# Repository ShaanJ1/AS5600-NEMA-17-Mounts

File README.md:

# AS5600 Nema 17 Mounts

Mounting hardware for attaching the AS5600 rotary encoder onto the back of the NEMA 17 stepper motor
Includes a magnet centering jig which helps you properly center the magnet onto the rear shaft to glue it in place

## Mounting Options:
### 1. Custom PCB + Spacers
Parts required:
- Diametric magnet
- Super glue (or equivalent strong adhesive)
- 4x M3 Machine Screws
- Custom AS5600 breakout board
- 4x Spacers

Installation Steps:

### 2. Custom mount for the AS5600
Parts Required:
- Diametric magnet
- Super glue (or equivalent strong adhesive)
- 3D printed sensor housing
- Regular AS5600 PCB
- 4x M2.5 screws

Installation Steps:

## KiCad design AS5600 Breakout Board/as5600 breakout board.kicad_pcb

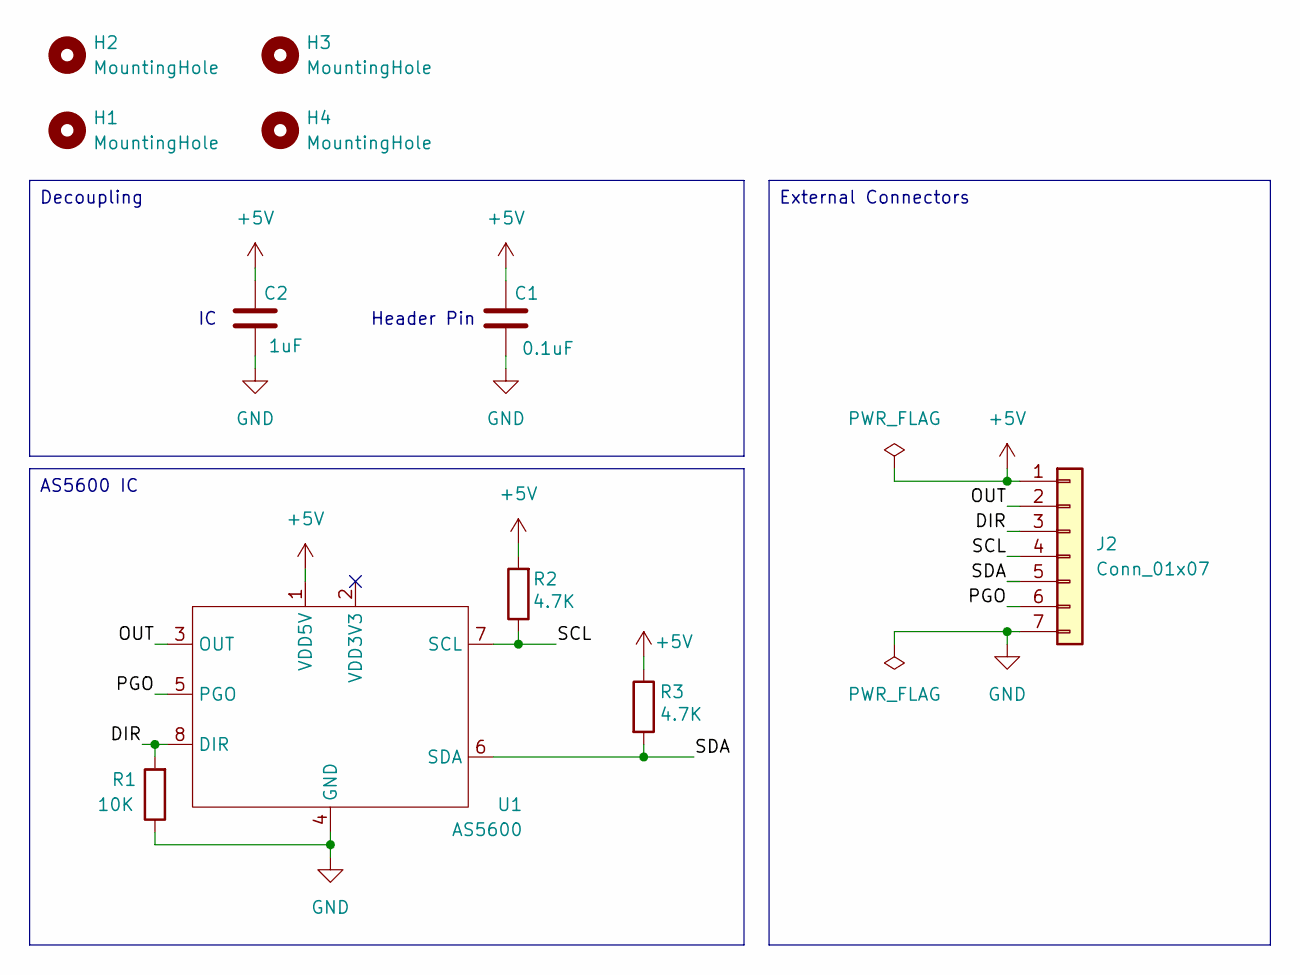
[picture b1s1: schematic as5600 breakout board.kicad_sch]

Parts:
C1: 0.1uF; C_0603_1608Metric
C2: 1uF; C_0603_1608Metric
H1, H2, H3, H4: MountingHole; MountingHole_3.2mm_M3
J2: Conn_01x07; PinHeader_1x07_P2.54mm_Horizontal
R1: 10K; R_0603_1608Metric
R2, R3: 4.7K; R_0603_1608Metric
U1: AS5600; SOIC-8_3.9x4.9mm_P1.27mm

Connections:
+5V: C1.1, C2.1, J2.1, R2.2, R3.1, U1.1 (VDD5V)
/DIR: J2.3, R1.2, U1.8 (DIR)
/OUT: J2.2, U1.3 (OUT)
/PGO: J2.6, U1.5 (PGO)
/SCL: J2.4, R2.1, U1.7 (SCL)
/SDA: J2.5, R3.2, U1.6 (SDA)
GND: C1.2, C2.2, J2.7, R1.1, U1.4 (GND)

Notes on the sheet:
Header Pin
Decoupling
External Connectors
AS5600 IC

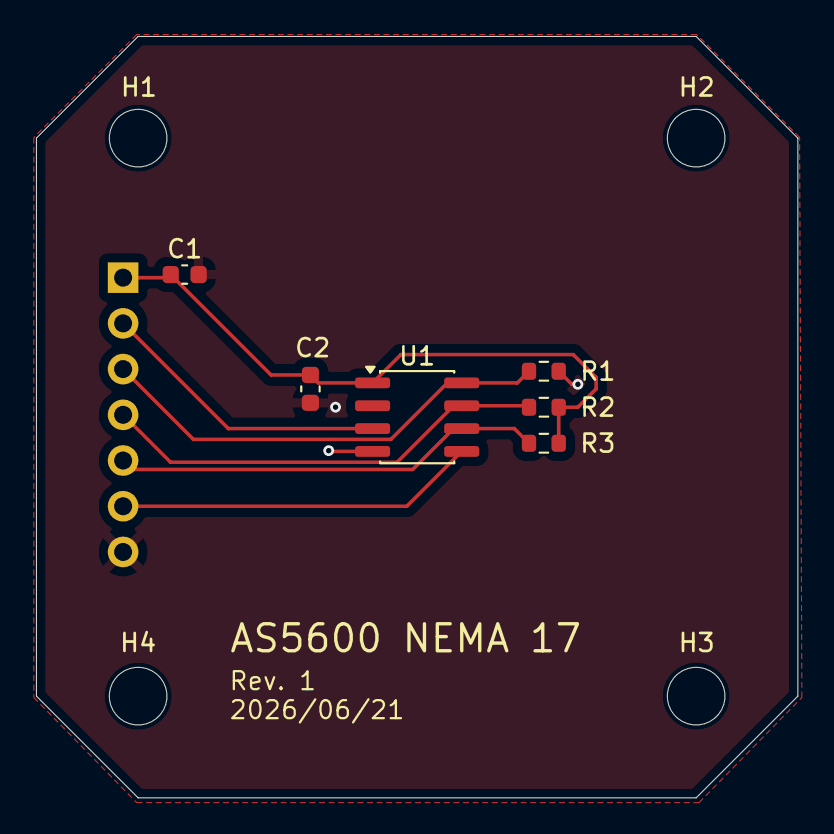
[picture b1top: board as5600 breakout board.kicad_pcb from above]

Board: 2 copper layers, 42.3 x 42.3 mm, 11 parts (1 on the bottom side), 7 nets.

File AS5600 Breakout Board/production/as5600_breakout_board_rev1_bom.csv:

Designator,Footprint,Quantity,Value,LCSC Part #
C1,0603,1,0.1uF,
C2,0603,1,1uF,
J2,PinHeader_1x07_P2.54mm_Horizontal,1,Conn_01x07,
R1,0603,1,10K,
"R2, R3",0603,2,4.7K,
U1,SOIC-8_3.9x4.9mm_P1.27mm,1,AS5600,

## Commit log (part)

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2026-06-22 Added project files
